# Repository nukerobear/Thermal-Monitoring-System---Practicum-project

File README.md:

Thermal-Monitoring-System---Practicum-project
=============================================

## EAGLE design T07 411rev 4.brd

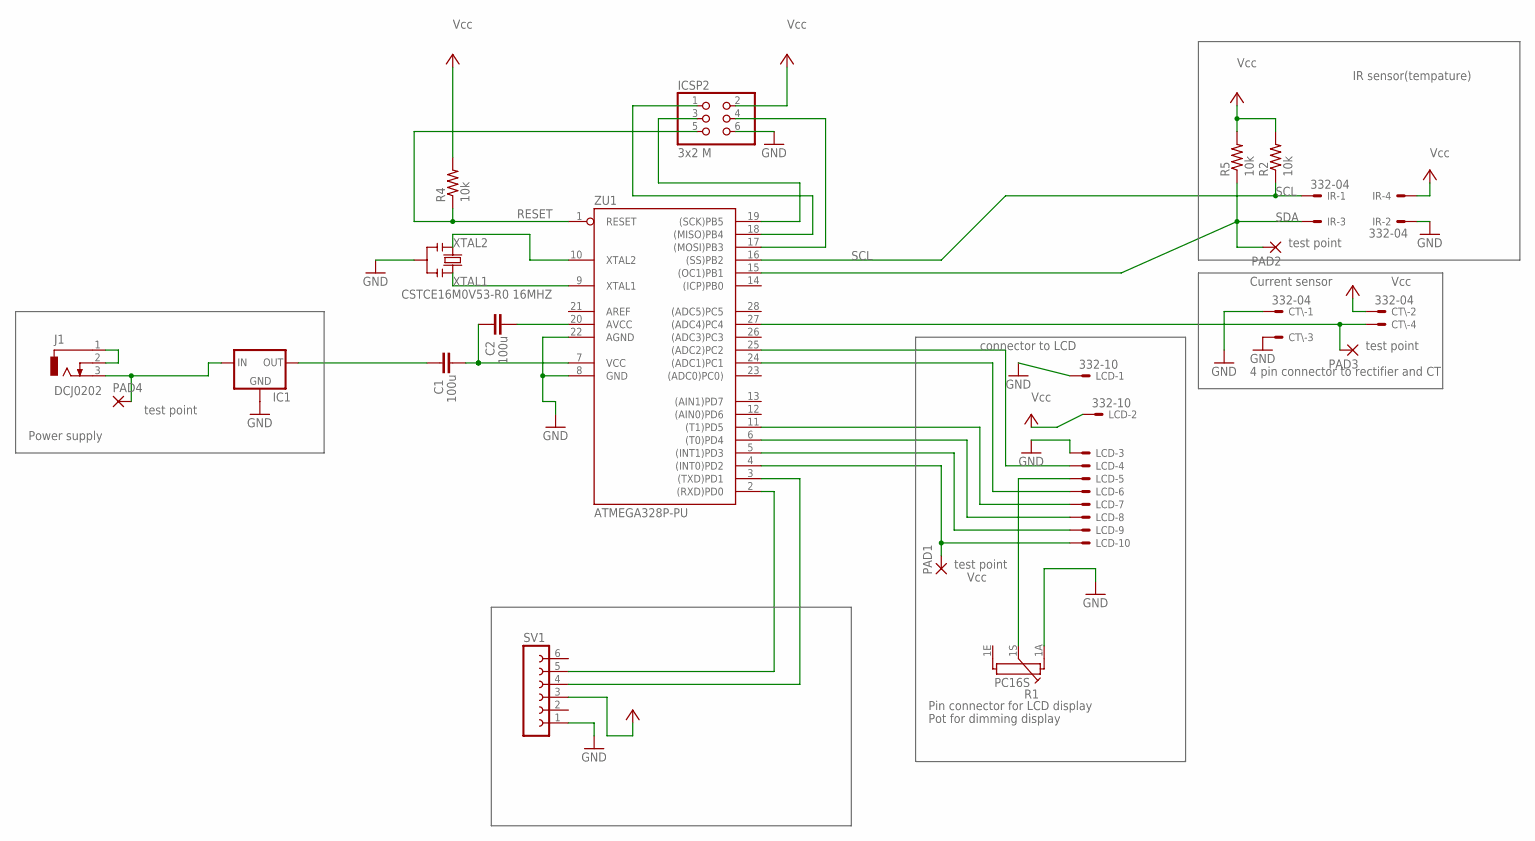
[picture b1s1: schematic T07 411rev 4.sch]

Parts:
C1, C2: 100u; C0603-ROUND
CT\: 332-04
IC1: 78XXL
ICSP2: 3x2 M; 2X03
IR: 332-04
J1: DCJ0202
LCD: 332-10
PAD1, PAD2, PAD3, PAD4: 1,6/0,9
R1: PC16S
R2, R4, R5: 10k; 0402-RES
SV1: FE06-1; FE06
Y3: CSTCE16M0V53-R0 16MHZ; RESONATOR
ZU1: ATMEGA328P-PU; DIL28-3

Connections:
+5V: CT\.2, ICSP2.2, IR.4, LCD.2, R2.2, R4.2, R5.2, SV1.3
GND: CT\.1, CT\.3, IC1.GND, ICSP2.6, IR.2, LCD.1, LCD.3, R1.1A, SV1.1, Y3.2, ZU1.8 (GND), ZU1.22 (AGND)
MISO1: ICSP2.1, ZU1.18 ((MISO)PB4)
MOSI1: ICSP2.4, ZU1.17 ((MOSI)PB3)
unnamed: LCD.10, PAD1.1, ZU1.4 ((INT0)PD2)
unnamed: LCD.9, ZU1.5 ((INT1)PD3)
unnamed: LCD.8, ZU1.6 ((T0)PD4)
unnamed: LCD.7, ZU1.11 ((T1)PD5)
unnamed: LCD.6, ZU1.24 ((ADC1)PC1)
unnamed: LCD.4, ZU1.25 ((ADC2)PC2)
unnamed: LCD.5, R1.1S
unnamed: C1.2, IC1.OUT
unnamed: IC1.IN, J1.3, PAD4.1
unnamed: C1.1, C2.2, ZU1.7 (VCC)
unnamed: C2.1, ZU1.20 (AVCC)
unnamed: CT\.4, PAD3.1, ZU1.27 ((ADC4)PC4)
unnamed: J1.1, J1.2
unnamed: SV1.4, ZU1.3 ((TXD)PD1)
unnamed: SV1.5, ZU1.2 ((RXD)PD0)
RESET: ICSP2.5, R4.1, ZU1.1 (RESET)
SCK1: ICSP2.3, ZU1.19 ((SCK)PB5)
SCL: IR.1, R2.1, ZU1.16 ((SS)PB2)
SDA: IR.3, PAD2.1, R5.1, ZU1.15 ((OC1)PB1)
XTAL1: Y3.3, ZU1.9 (XTAL1)
XTAL2: Y3.1, ZU1.10 (XTAL2)

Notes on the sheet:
connector to LCD
IR sensor(tempature)
Power supply
Current sensor
4 pin connector to rectifier and CT
Pin connector for LCD display
Pot for dimming display
Vcc
test point

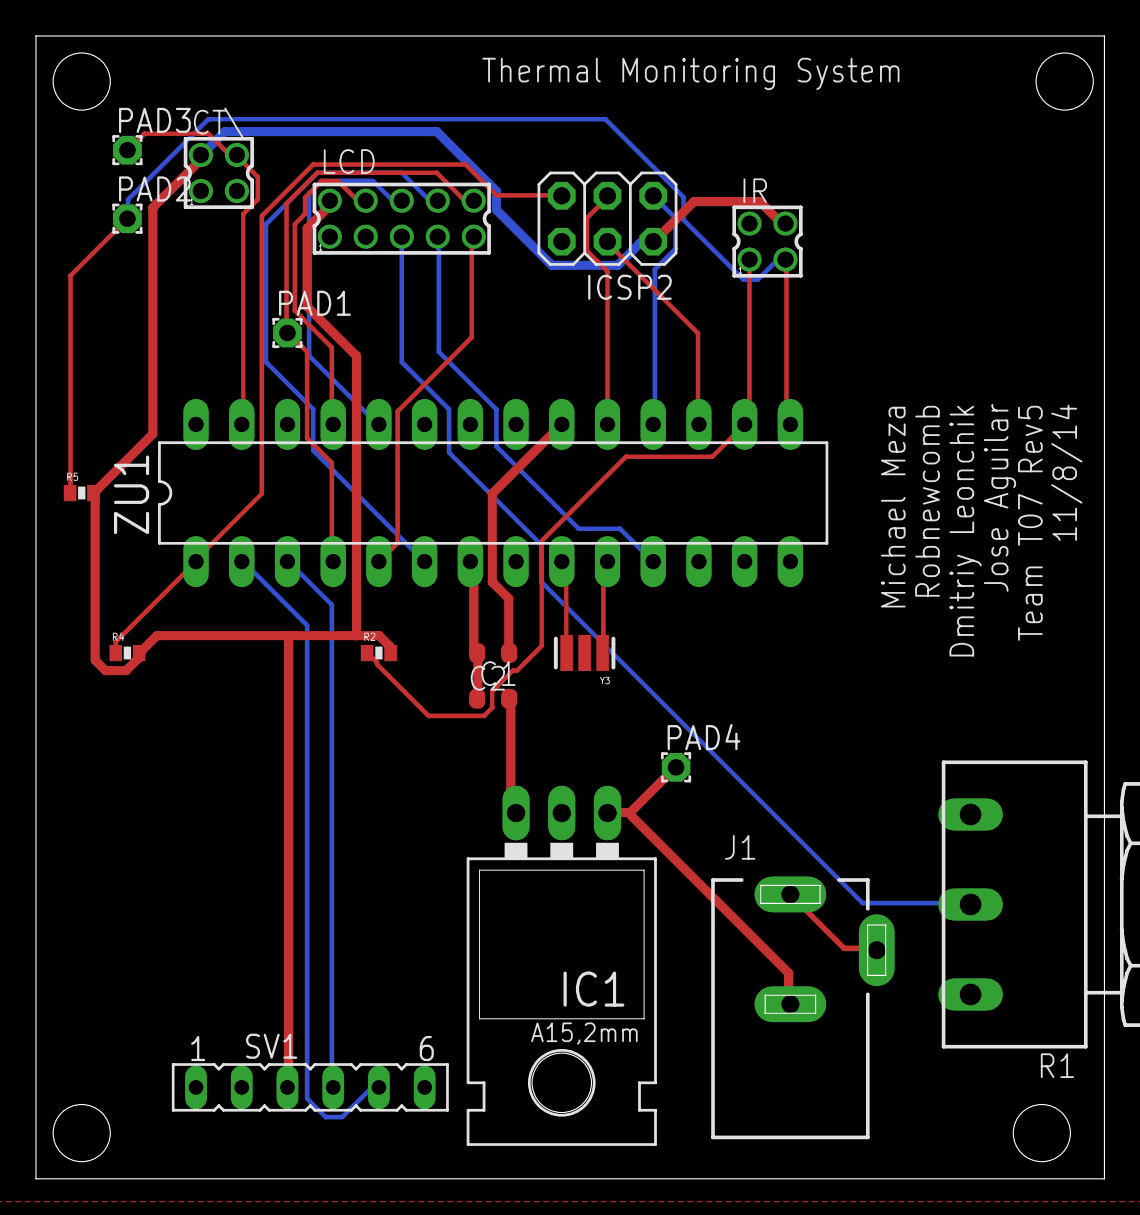
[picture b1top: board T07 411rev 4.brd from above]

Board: 2 copper layers, 59.4 x 63.5 mm, 19 parts (0 on the bottom side), 25 nets.

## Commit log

2014-10-25 Test Commit.
2014-10-25 Delete Test push.txt
    Clearing test.
2014-10-26 Practicum Project Proposals
2014-10-28 First Copy of the PDS
2014-10-29 Schematic of 411 Project
2014-10-29 Schematic of 411 Project T07
2014-11-01 Weekly Progress Reports
2014-11-05 T07 Schematic due 11/5
2014-11-05 Preliminary Board Layout Due 11/5
2014-11-06 T07 Preliminary Schematic Due 11/5 Rev.2
2014-11-10 Practicum Project WBS Rev3
2014-11-10 Practicum Project WBS T07 Rev 3.1
2014-11-14 Team Meeting updates
2014-11-16 T07 Block Daigram
2014-11-17 HW #5
2014-11-18 Team Meeting 11/18/14
2014-11-24 T07 Test Plan
2014-12-11 Final Project Documents
2014-12-11 Board Layout and schematic T07
